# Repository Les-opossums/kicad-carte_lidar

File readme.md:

# Carte lidar - opossum 2025

Cette carte se trouve dans le mat de balise du robot opossum.
Elle doit : 
- Gérer le lidar A2M12 (alimentation + récupération des données).
- Gérer un accéléromètre mpu-6000 et l'utiliser pour corriger les points lidar.
- Gérer le ruban led qui entoure le mat de balise
La communication avec le raspberry pi se fait soit par USB (également utilisé pour programmer le rp2040) soit via ethernet avec un module W5500.

On peut également y brancher 3 TOFs de type vl53l0x et une carte d'extension i2c pour en brancher plus. 

L'alimentation du rp2040 se fait au choix soit par la tension d'entrée 24v également utilisée par le lidar, soit par l'usb.

## Intégration mécanique dans le robot 
Voici un appercu de la carte dans le mat de balise du robot :

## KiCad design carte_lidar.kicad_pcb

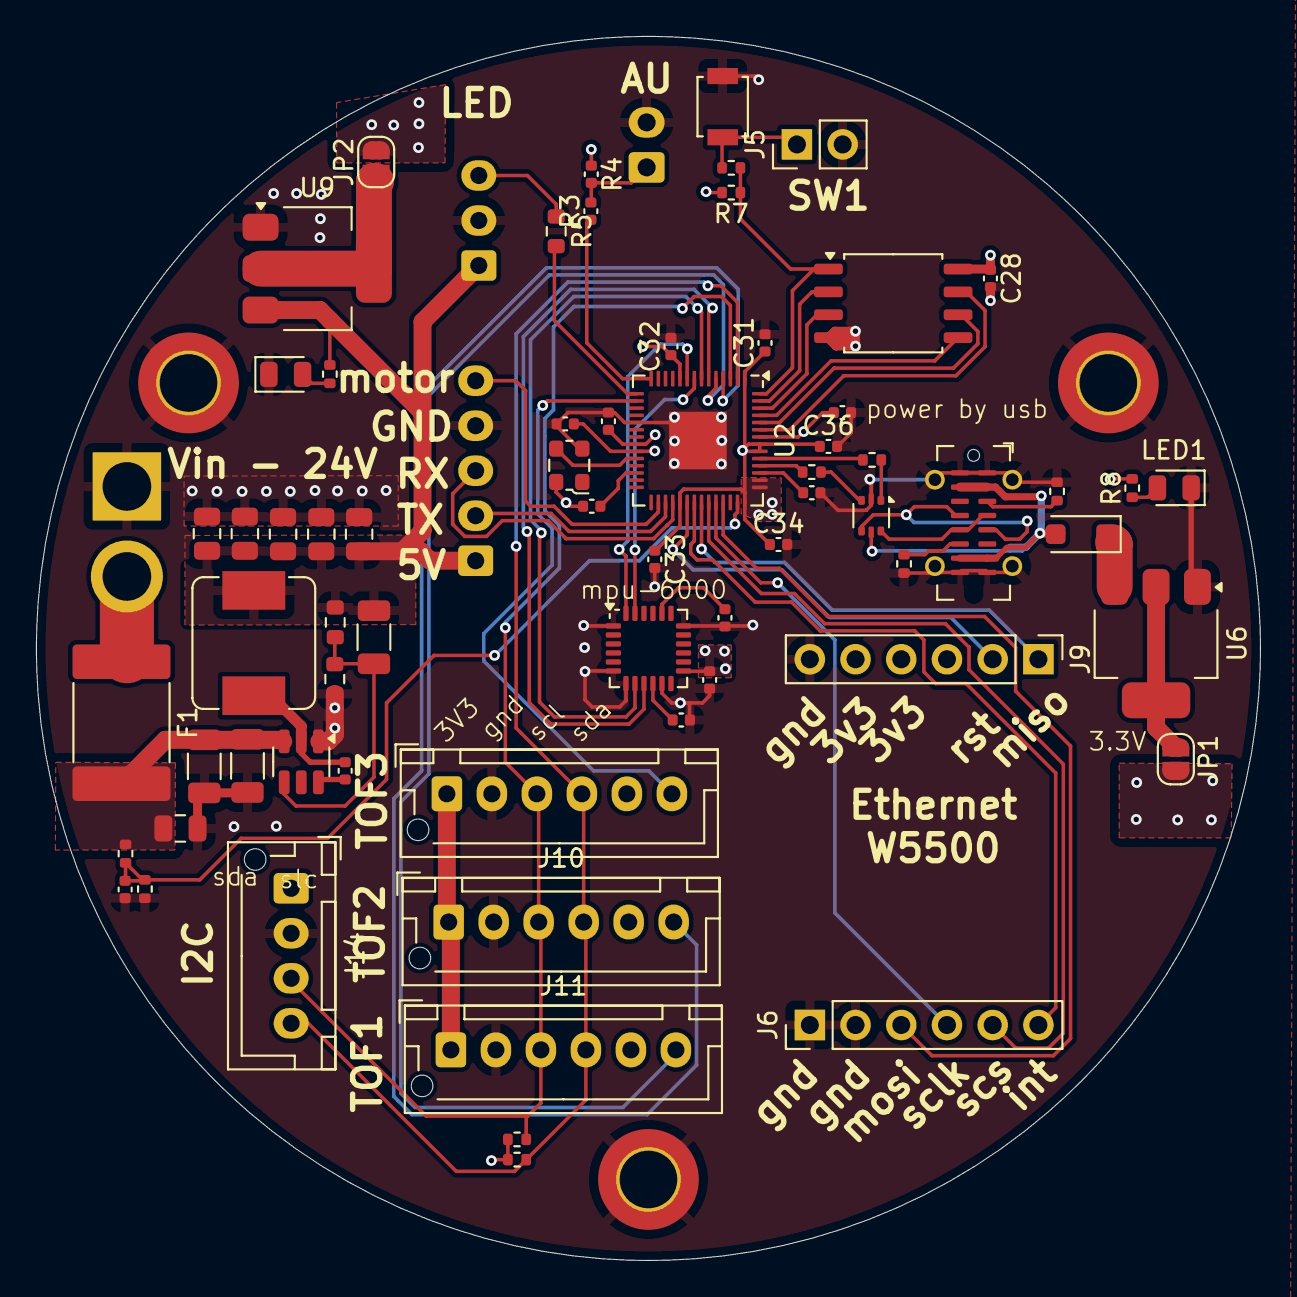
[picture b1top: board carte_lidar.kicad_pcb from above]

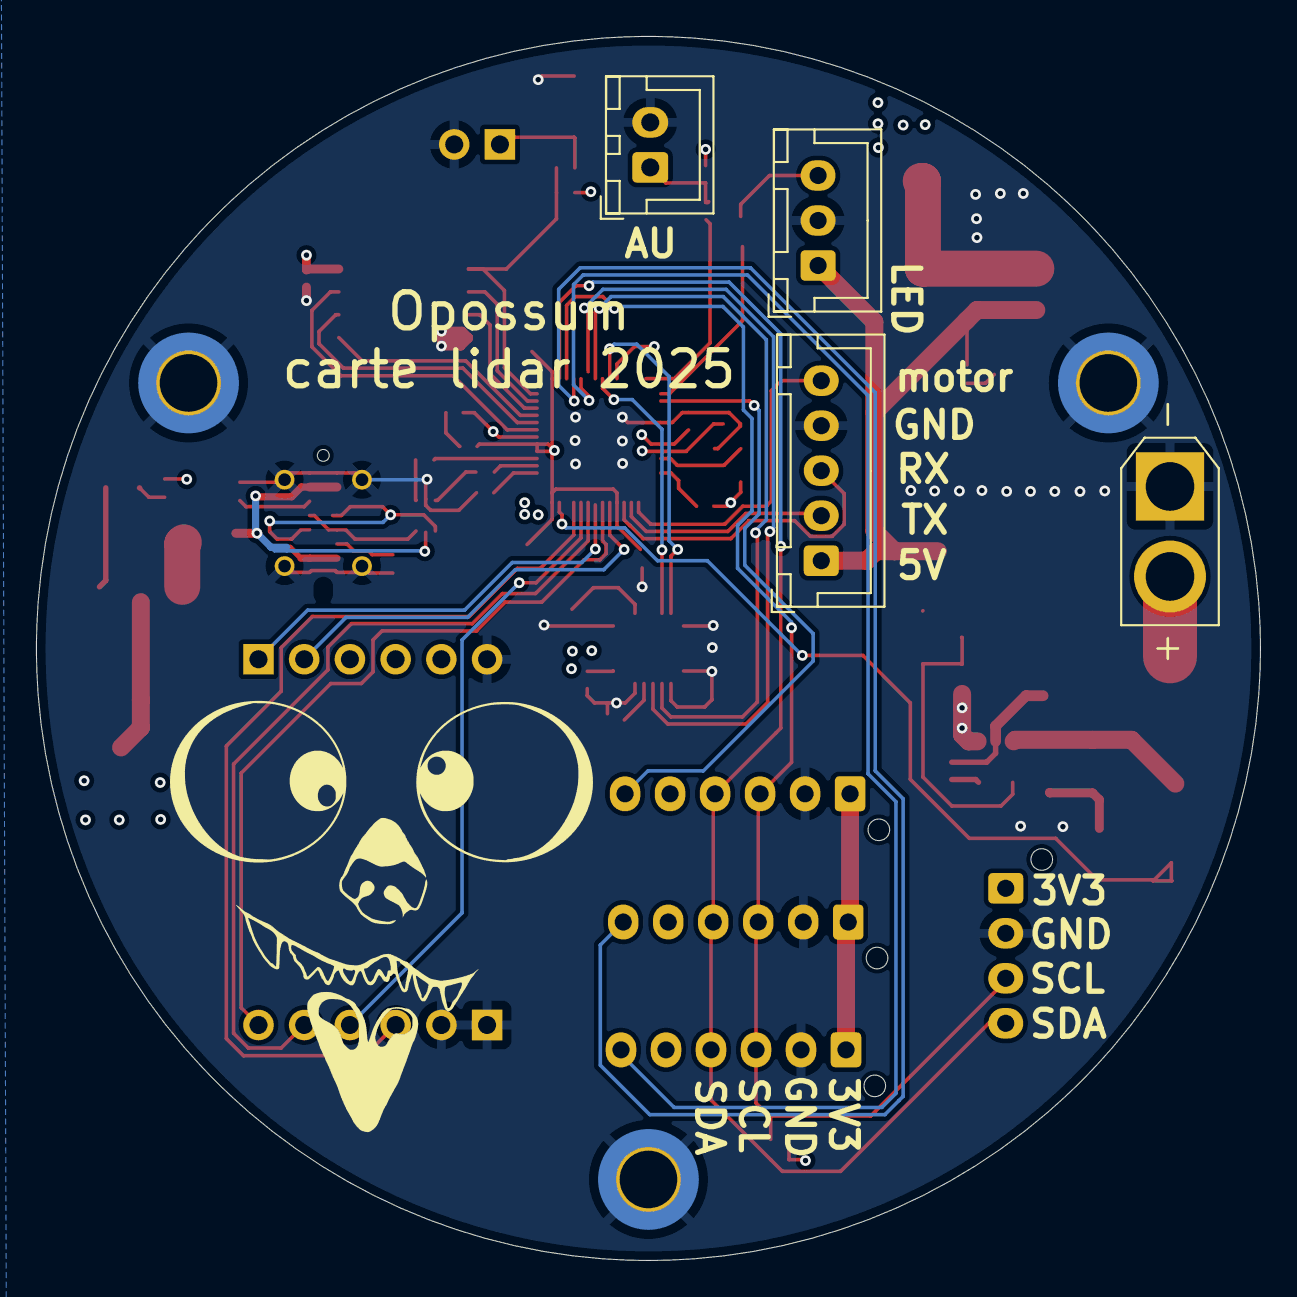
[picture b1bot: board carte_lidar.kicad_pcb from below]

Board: 4 copper layers, 68.0 x 68.0 mm, 73 parts (4 on the bottom side), 58 nets.

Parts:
C1, C2: 10µF 50V; C_1206_3216Metric
C3: 100nF 50V; C_0805_2012Metric
C4: 100nF 50V; C_0402_1005Metric
C5: 150pF 50V; C_1206_3216Metric
C6, C7, C8, C9, C10: 22µF 25V; C_0805_2012Metric
C21, C24, C25, C27: 0.1uF 10V; C_0402_1005Metric
C22: 220nF 50V; C_0402_1005Metric
C23: 2.2nF 10V; C_0402_1005Metric
C26, C31, C32, C33, C34, C35, C36: 1uF 6.3V; C_0402_1005Metric
C28: 220nF 16V; C_0402_1005Metric
D1: MBR120VLSFT1G; D_SOD-123F
F1: JK-SMD300L-24V; Fuse_2920_7451Metric
H1, H2, H3: MountingHole_Pad; MountingHole_3.2mm_M3_DIN965_Pad_TopBottom
J1: Conn_01x03_Pin; JST_XH_B3B-XH-A_1x03_P2.50mm_Vertical
J2: Conn_01x02_Pin; AMASS_XT30U-F_1x02_P5.0mm_Vertical
J3: Conn_01x05_Socket; JST_XH_B5B-XH-A_1x05_P2.50mm_Vertical
J4: Conn_01x02; JST_XH_B2B-XH-A_1x02_P2.50mm_Vertical
J5: Conn_01x02_Pin; PinHeader_1x02_P2.54mm_Vertical
J6, J9: Conn_01x06_Socket; PinHeader_1x06_P2.54mm_Vertical
J8: USB_C_Receptacle_USB2.0_16P; USB_C_Receptacle_G-Switch_GT-USB-7051x
J10, J11, J12: Conn_01x06_Socket; JST_XH_B6B-XH-AM_1x06_P2.50mm_Vertical
J14: Conn_01x04_Socket; JST_XH_B4B-XH-AM_1x04_P2.50mm_Vertical
JP1, JP2: SolderJumper_2_Open; SolderJumper-2_P1.3mm_Open_RoundedPad1.0x1.5mm
L1: PSPMAQ0605H-150M-ANP; Prod_Tech_7.1x6.6mm
LED1, LED2: YELLOW; LED_0805_2012Metric
R1: 100k; R_0603_1608Metric
R2: 13.3k; R_0603_1608Metric
R3: 100R; C_0402_1005Metric
R4, R16: 10k; C_0402_1005Metric
R5: 330R; R_0603_1608Metric
R6, R8, R15, R18: 1k; R_0402_1005Metric
R7: 100k; R_0402_1005Metric
R11, R12: 5.1k; R_0402_1005Metric
R13, R14: 27R; R_0402_1005Metric
R17: 10k; R_0402_1005Metric
R24, R25: 4.7k; R_0402_1005Metric
SW1: SW_Push; SW_SPST_B3U-1000P
U1: TPS54302; SOT-23-6
U2: RP2040; QFN-56-1EP_7x7mm_P0.4mm_EP3.2x3.2mm
U3: W25Q128JVS; SOIC-8_5.23x5.23mm_P1.27mm
U5: USBLC6-2P6; SOT-666
U6, U9: NM/AMS1117-3.3; SOT-223-3_TabPin2
U7: MPU-6000; InvenSense_QFN-24_4x4mm_P0.5mm
X1: S2D12.000000B20F30T; Oscillator_SMD_ECS_2520MV-xxx-xx-4Pin_2.5x2.0mm

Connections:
5V_USB: D1.1 (K), U6.3 (VI)
+3V3: C24.1, C28.1, C31.1, C32.1, C33.1, C34.1, C35.1, C36.1, J9.4, J9.5, J10.1, J11.1, J12.1, J14.1, JP1.2 (B), JP2.2 (B), R4.1, R7.2, R8.2, R16.1, R24.2, R25.2, U2.1 (IOVDD), U2.10 (IOVDD), U2.22 (IOVDD), U2.33 (IOVDD), U2.42 (IOVDD), U2.43 (ADC_AVDD), U2.44 (VREG_IN), U2.48 (USB_VDD), U2.49 (IOVDD), U3.8 (VCC), U7.13 (VDD), X1.4 (VDD)
+5V: C5.1, C6.1, C7.1, C8.1, C9.1, C10.1, J1.1, J3.1, L1.2, R1.1, R15.2, U9.3 (VI)
/+1.1V: C25.1, C27.1, U2.23 (DVDD), U2.50 (DVDD)
/AU: R3.1, U2.14 (GPIO11)
/CSn: U2.7 (GPIO5), U7.8 (~CS)
/Clk_12MHz: U2.24 (SWCLK), X1.3 (OUT)
/MISO: U2.6 (GPIO4), U7.9 (AD0/MISO)
/MOSI: U2.9 (GPIO7), U7.24 (SDA/MOSI)
/SCLK: U2.8 (GPIO6), U7.23 (SCL/SCLK)
/led: R5.2, U2.15 (GPIO12)
/lidar_rx: J3.3, U2.32 (GPIO21)
/lidar_tx: J3.2, U2.31 (GPIO20)
/motoct: J3.5, U2.30 (GPIO19)
/power/VBAT: F1.1, J2.2
/power/VBAT_FUZED: C1.1, C2.1, C3.1, F1.2, R17.2, U1.3 (VIN)
BAT_SENSE: C22.1, R17.1, R18.2, U2.41 (GPIO29_ADC3)
GND: C1.2, C2.2, C3.2, C6.2, C7.2, C8.2, C9.2, C10.2, C21.2, C22.2, C23.2, C24.2, C25.2, C26.2, C27.2, C28.2, C31.2, C32.2, C33.2, C34.2, C35.2, C36.2, H1.1, H2.1, H3.1, J1.2, J2.1, J3.4, J4.2, J5.2, J6.1, J6.2, J8.A1 (GND), J8.A12 (GND), J8.B1 (GND), J8.B12 (GND), J8.S1 (SHIELD), J9.6, J10.2, J11.2, J12.2, J14.2, LED1.1 (K), LED2.1 (K), R2.2, R11.2, R12.2, R18.1, SW1.1, U1.1 (GND), U2.19 (TESTEN), U2.57 (GND), U3.4 (GND), U5.2 (GND), U6.1 (GND), U7.1 (CLKIN), U7.6 (AUX_DA), U7.7 (AUX_CL), U7.11 (FSYNC), U7.18 (GND), U9.1 (GND), X1.2 (GND)
unnamed: D1.2 (A), J8.A4 (VBUS), J8.A9 (VBUS), J8.B4 (VBUS), J8.B9 (VBUS), U5.5 (VBUS)
unnamed: J1.3, R5.1
unnamed: J4.1, R3.2, R4.2
unnamed: J5.1, R6.2, SW1.2
unnamed: J8.A5 (CC1), R11.1
unnamed: J8.B5 (CC2), R12.1
unnamed: J8.A6 (D+), J8.B6 (D+), U5.6 (I/O1)
unnamed: J8.A7 (D-), J8.B7 (D-), U5.4 (I/O2)
unnamed: JP1.1 (A), U6.2 (VO)
unnamed: JP2.1 (A), U9.2 (VO)
unnamed: LED1.2 (A), R8.1
unnamed: LED2.2 (A), R15.1
unnamed: R13.1, U5.3 (I/O2)
unnamed: R14.1, U5.1 (I/O1)
unnamed: C4.1, U1.6 (BOOT)
unnamed: C5.2, R1.2, R2.1, U1.4 (FB)
unnamed: C4.2, L1.1, U1.2 (SW)
unnamed: U2.52 (QSPI_SCLK), U3.6 (CLK)
unnamed: U2.53 (QSPI_SD0), U3.5 (DI(IO0))
unnamed: U2.55 (QSPI_SD1), U3.2 (DO(IO1))
unnamed: U2.54 (QSPI_SD2), U3.3 (IO2)
unnamed: U2.51 (QSPI_SD3), U3.7 (IO3)
unnamed: R6.1, R7.1, U2.56 (QSPI_SS), U3.1 (~CS)
unnamed: R16.2, U2.26 (RUN)
unnamed: C26.1, U2.45 (VREG_VOUT)
unnamed: C23.1, U7.20 (CPOUT)
unnamed: C21.1, U7.10 (REGOUT)
USB_N: R13.2, U2.46 (USB_DM)
USB_P: R14.2, U2.47 (USB_DP)
eth_int: J6.6, U2.35 (GPIO23)
eth_miso: J9.1, U2.36 (GPIO24)
eth_mosi: J6.3, U2.39 (GPIO27_ADC1)
eth_rst: J9.2, U2.34 (GPIO22)
eth_sclk: J6.4, U2.38 (GPIO26_ADC0)
eth_scs: J6.5, U2.37 (GPIO25)
scl: J10.3, J11.3, J12.3, J14.3, R25.1, U2.3 (GPIO1)
sda: J10.4, J11.4, J12.4, J14.4, R24.1, U2.2 (GPIO0)
tof1: J11.6, U2.5 (GPIO3)
tof2: J10.6, U2.4 (GPIO2)
tof3: J12.6, U2.16 (GPIO13)

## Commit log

2024-12-08 first commit only for cao
2024-12-24 update all
2024-12-26 add ethernet in schematic
2024-12-29 update silkscreen layer
2024-12-29 add readme
